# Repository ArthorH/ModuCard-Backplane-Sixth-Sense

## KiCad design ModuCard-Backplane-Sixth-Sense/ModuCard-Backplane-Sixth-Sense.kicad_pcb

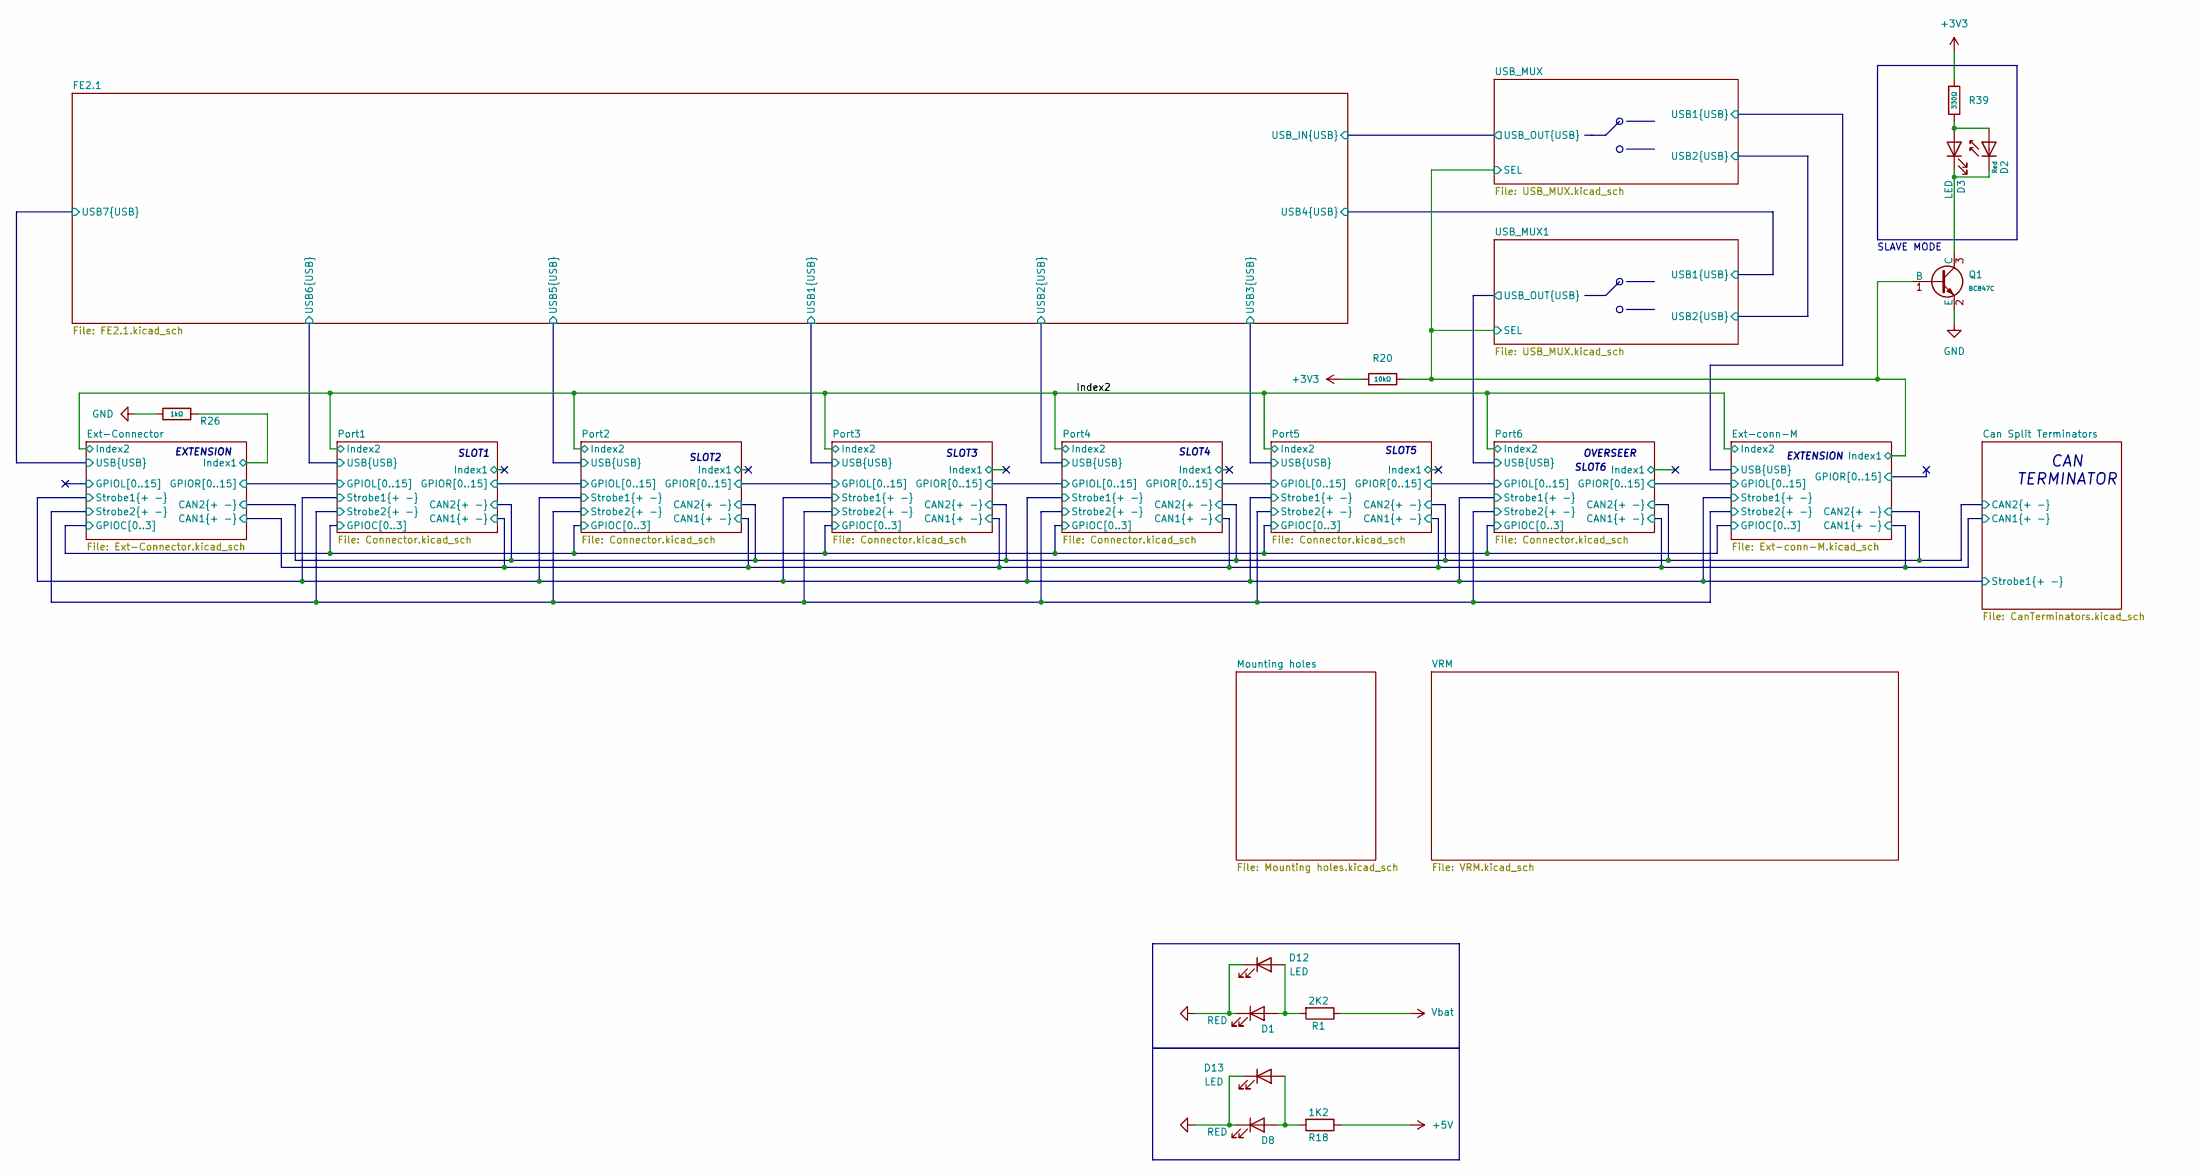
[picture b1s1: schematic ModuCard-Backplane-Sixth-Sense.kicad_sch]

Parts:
D1, D8: RED; D_0402_1005Metric
D2: Red; D_0603; Part KT-0603R; LCSC C2286
D3: LED; LED_D3.0mm_Clear
D12, D13: LED; LED_D3.0mm
Q1: BC847C; Q_SOT-23; Part BC847C; LCSC C7420337
R1: 2K2; R_0402_1005Metric
R18: 1K2; R_0402_1005Metric
R20: 10kΩ; R_0402; Overload Voltage (Max) 50V; Tolerance ±1%; Part 0402WGF1002TCE; LCSC C25744
R26: 1kΩ; R_0402; Overload Voltage (Max) 50V; Tolerance ±1%; Part 0402WGF1001TCE; LCSC C11702
R39: 330Ω; R_0402; Overload Voltage (Max) 50V; Tolerance ±1%; Part 0402WGF3300TCE; LCSC C25104

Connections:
+3V3: R20.1, R39.1; also elsewhere on the board
+5V: R18.1; also elsewhere on the board
/Ext-Connector/Index1: R26.1; also elsewhere on the board
/Ext-conn-M/Index1: Q1.1 (B), R20.2; also elsewhere on the board
GND: D1.1 (K), D8.1 (K), D12.1 (K), D13.1 (K), Q1.2 (E), R26.2; also elsewhere on the board
unnamed: D1.2 (A), D12.2 (A), R1.2
unnamed: D2.2, D3.2 (A), R39.2
unnamed: D2.1, D3.1 (K), Q1.3 (C)
unnamed: D8.2 (A), D13.2 (A), R18.2
Vbat: R1.1; also elsewhere on the board

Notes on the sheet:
CAN TERMINATOR
SLOT4
SLAVE MODE
OVERSEER
SLOT3
SLOT6
EXTENSION
SLOT2
SLOT5
SLOT1

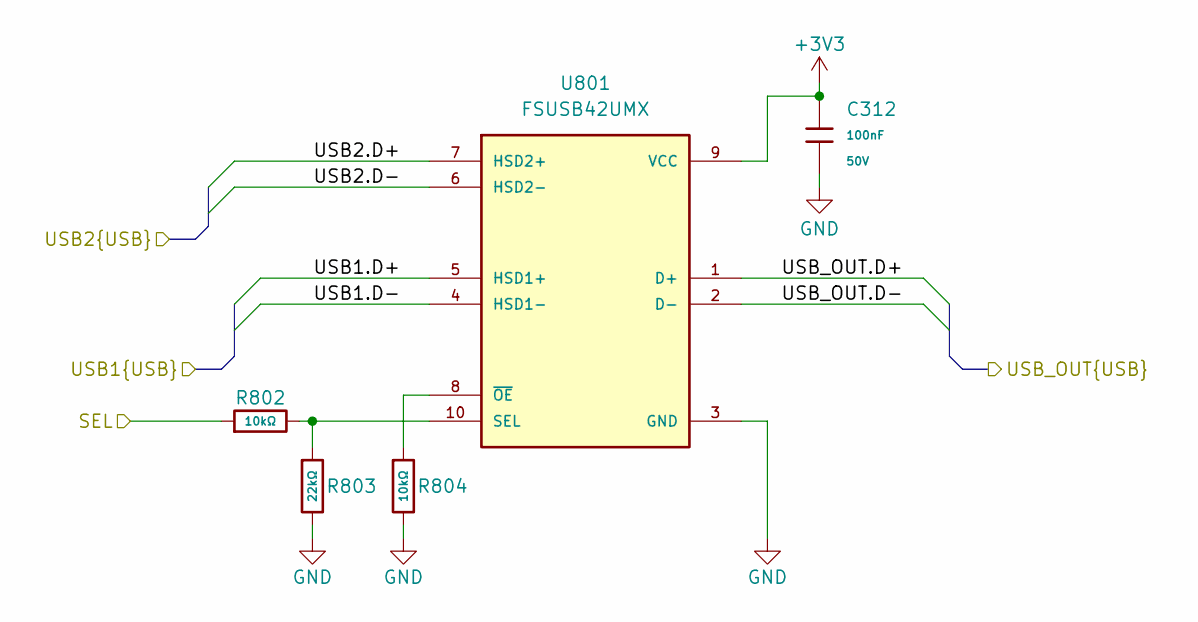
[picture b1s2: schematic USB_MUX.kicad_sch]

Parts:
C312: 100nF; C_0402; Voltage Rated 50V; Tolerance ±10%; Part CL05B104KB54PNC; LCSC C307331
R802, R804: 10kΩ; R_0402; Overload Voltage (Max) 50V; Tolerance ±1%; Part 0402WGF1002TCE; LCSC C25744
R803: 22kΩ; R_0402; Overload Voltage (Max) 50V; Tolerance ±1%; Part 0402WGF2202TCE; LCSC C25768
U801: FSUSB42UMX; UQFN-10_1.4x1.8mm_P0.4mm; PARTREV 1.25; LCSC C49186231

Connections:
+3V3: C312.1, U801.9 (VCC); also elsewhere on the board
/Ext-conn-M/Index1: R802.1; also elsewhere on the board
/Ext-conn-M/USB.D+: U801.5 (HSD1+); also elsewhere on the board
/Ext-conn-M/USB.D-: U801.4 (HSD1-); also elsewhere on the board
/FE2.1/USB_IN.D+: U801.1 (D+); also elsewhere on the board
/FE2.1/USB_IN.D-: U801.2 (D-); also elsewhere on the board
/USB_MUX/USB2.D+: U801.7 (HSD2+); also elsewhere on the board
/USB_MUX/USB2.D-: U801.6 (HSD2-); also elsewhere on the board
GND: C312.2, R803.2, R804.2, U801.3 (GND); also elsewhere on the board
unnamed: R802.2, R803.1, U801.10 (SEL)
unnamed: R804.1, U801.8 (~OE)

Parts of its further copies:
C313: 100nF; C_0402; Voltage Rated 50V; Tolerance ±10%; Part CL05B104KB54PNC; LCSC C307331
R805, R807: 10kΩ; R_0402; Overload Voltage (Max) 50V; Tolerance ±1%; Part 0402WGF1002TCE; LCSC C25744
R806: 22kΩ; R_0402; Overload Voltage (Max) 50V; Tolerance ±1%; Part 0402WGF2202TCE; LCSC C25768
U802: FSUSB42UMX; UQFN-10_1.4x1.8mm_P0.4mm; PARTREV 1.25; LCSC C49186231

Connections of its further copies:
+3V3: C313.1, U802.9 (VCC); also elsewhere on the board
/Ext-conn-M/Index1: R805.1; also elsewhere on the board
/FE2.1/USB4.D+: U802.5 (HSD1+); also elsewhere on the board
/FE2.1/USB4.D-: U802.4 (HSD1-); also elsewhere on the board
/Port6/USB.D+: U802.1 (D+); also elsewhere on the board
/Port6/USB.D-: U802.2 (D-); also elsewhere on the board
/USB_MUX/USB2.D+: U802.7 (HSD2+); also elsewhere on the board
/USB_MUX/USB2.D-: U802.6 (HSD2-); also elsewhere on the board
GND: C313.2, R806.2, R807.2, U802.3 (GND); also elsewhere on the board
unnamed: R805.2, R806.1, U802.10 (SEL)
unnamed: R807.1, U802.8 (~OE)

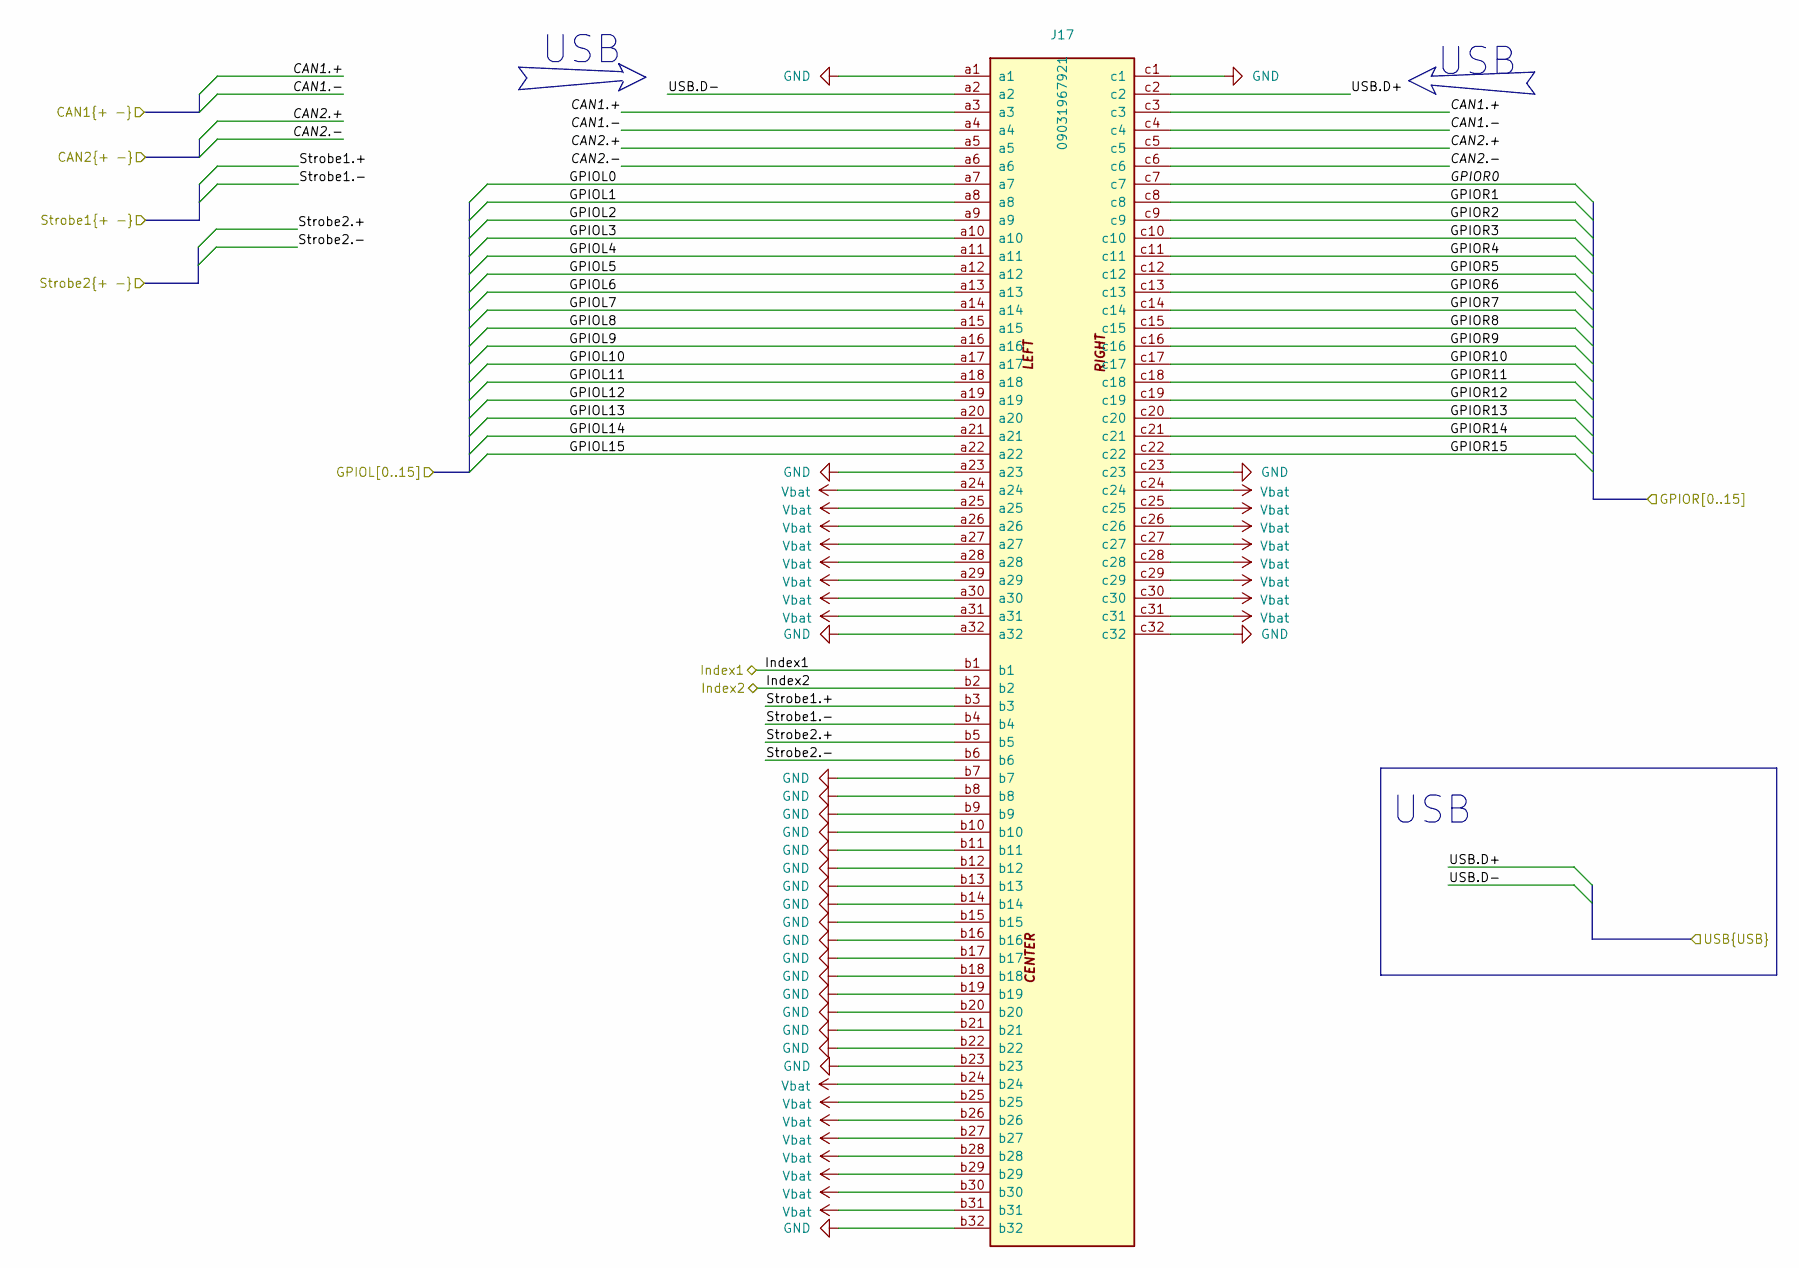
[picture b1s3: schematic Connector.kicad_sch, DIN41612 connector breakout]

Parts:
J17: 09031967921; DIN41612_R_3x32_Male_Vertical_THT; PARTREV D

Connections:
/Can Split Terminators/CAN1.+: J17.a3, J17.c3; also elsewhere on the board
/Can Split Terminators/CAN1.-: J17.a4, J17.c4; also elsewhere on the board
/Can Split Terminators/CAN2.+: J17.a5, J17.c5; also elsewhere on the board
/Can Split Terminators/CAN2.-: J17.a6, J17.c6; also elsewhere on the board
/Can Split Terminators/Strobe1.+: J17.b3; also elsewhere on the board
/Can Split Terminators/Strobe1.-: J17.b4; also elsewhere on the board
/Ext-Connector/Strobe2.+: J17.b5; also elsewhere on the board
/Ext-Connector/Strobe2.-: J17.b6; also elsewhere on the board
/FE2.1/USB5.D+: J17.c2; also elsewhere on the board
/FE2.1/USB5.D-: J17.a2; also elsewhere on the board
/Index2: J17.b2; also elsewhere on the board
/Port1/GPIOR0: J17.a7; also elsewhere on the board
/Port1/GPIOR1: J17.a8; also elsewhere on the board
/Port1/GPIOR2: J17.a9; also elsewhere on the board
/Port1/GPIOR3: J17.a10; also elsewhere on the board
/Port1/GPIOR4: J17.a11; also elsewhere on the board
/Port1/GPIOR5: J17.a12; also elsewhere on the board
/Port1/GPIOR6: J17.a13; also elsewhere on the board
/Port1/GPIOR7: J17.a14; also elsewhere on the board
/Port1/GPIOR8: J17.a15; also elsewhere on the board
/Port1/GPIOR9: J17.a16; also elsewhere on the board
/Port1/GPIOR10: J17.a17; also elsewhere on the board
/Port1/GPIOR11: J17.a18; also elsewhere on the board
/Port1/GPIOR12: J17.a19; also elsewhere on the board
/Port1/GPIOR13: J17.a20; also elsewhere on the board
/Port1/GPIOR14: J17.a21; also elsewhere on the board
/Port1/GPIOR15: J17.a22; also elsewhere on the board
/Port2/GPIOR0: J17.c7; also elsewhere on the board
/Port2/GPIOR1: J17.c8; also elsewhere on the board
/Port2/GPIOR2: J17.c9; also elsewhere on the board
/Port2/GPIOR3: J17.c10; also elsewhere on the board
/Port2/GPIOR4: J17.c11; also elsewhere on the board
/Port2/GPIOR5: J17.c12; also elsewhere on the board
/Port2/GPIOR6: J17.c13; also elsewhere on the board
/Port2/GPIOR7: J17.c14; also elsewhere on the board
/Port2/GPIOR8: J17.c15; also elsewhere on the board
/Port2/GPIOR9: J17.c16; also elsewhere on the board
/Port2/GPIOR10: J17.c17; also elsewhere on the board
/Port2/GPIOR11: J17.c18; also elsewhere on the board
/Port2/GPIOR12: J17.c19; also elsewhere on the board
/Port2/GPIOR13: J17.c20; also elsewhere on the board
/Port2/GPIOR14: J17.c21; also elsewhere on the board
/Port2/GPIOR15: J17.c22; also elsewhere on the board
/Port2/Index1: J17.b1
GND: J17.a1, J17.a23, J17.a32, J17.b7, J17.b8, J17.b9, J17.b10, J17.b11, J17.b12, J17.b13, J17.b14, J17.b15, J17.b16, J17.b17, J17.b18, J17.b19, J17.b20, J17.b21, J17.b22, J17.b23, J17.b32, J17.c1, J17.c23, J17.c32; also elsewhere on the board
Vbat: J17.a24, J17.a25, J17.a26, J17.a27, J17.a28, J17.a29, J17.a30, J17.a31, J17.b24, J17.b25, J17.b26, J17.b27, J17.b28, J17.b29, J17.b30, J17.b31, J17.c24, J17.c25, J17.c26, J17.c27, J17.c28, J17.c29, J17.c30, J17.c31; also elsewhere on the board

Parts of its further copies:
J16, J18, J19, J20, J21: 09031967921; DIN41612_R_3x32_Male_Vertical_THT; PARTREV D

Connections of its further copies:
/Can Split Terminators/CAN1.+: J16.a3, J16.c3, J18.a3, J18.c3, J19.a3, J19.c3, J20.a3, J20.c3, J21.a3, J21.c3; also elsewhere on the board
/Can Split Terminators/CAN1.-: J16.a4, J16.c4, J18.a4, J18.c4, J19.a4, J19.c4, J20.a4, J20.c4, J21.a4, J21.c4; also elsewhere on the board
/Can Split Terminators/CAN2.+: J16.a5, J16.c5, J18.a5, J18.c5, J19.a5, J19.c5, J20.a5, J20.c5, J21.a5, J21.c5; also elsewhere on the board
/Can Split Terminators/CAN2.-: J16.a6, J16.c6, J18.a6, J18.c6, J19.a6, J19.c6, J20.a6, J20.c6, J21.a6, J21.c6; also elsewhere on the board
/Can Split Terminators/Strobe1.+: J16.b3, J18.b3, J19.b3, J20.b3, J21.b3; also elsewhere on the board
/Can Split Terminators/Strobe1.-: J16.b4, J18.b4, J19.b4, J20.b4, J21.b4; also elsewhere on the board
/Ext-Connector/GPIOR0: J16.a7; also elsewhere on the board
/Ext-Connector/GPIOR1: J16.a8; also elsewhere on the board
/Ext-Connector/GPIOR2: J16.a9; also elsewhere on the board
/Ext-Connector/GPIOR3: J16.a10; also elsewhere on the board
/Ext-Connector/GPIOR4: J16.a11; also elsewhere on the board
/Ext-Connector/GPIOR5: J16.a12; also elsewhere on the board
/Ext-Connector/GPIOR6: J16.a13; also elsewhere on the board
/Ext-Connector/GPIOR7: J16.a14; also elsewhere on the board
/Ext-Connector/GPIOR8: J16.a15; also elsewhere on the board
/Ext-Connector/GPIOR9: J16.a16; also elsewhere on the board
/Ext-Connector/GPIOR10: J16.a17; also elsewhere on the board
/Ext-Connector/GPIOR11: J16.a18; also elsewhere on the board
/Ext-Connector/GPIOR12: J16.a19; also elsewhere on the board
/Ext-Connector/GPIOR13: J16.a20; also elsewhere on the board
/Ext-Connector/GPIOR14: J16.a21; also elsewhere on the board
/Ext-Connector/GPIOR15: J16.a22; also elsewhere on the board
/Ext-Connector/Strobe2.+: J16.b5, J18.b5, J19.b5, J20.b5, J21.b5; also elsewhere on the board
/Ext-Connector/Strobe2.-: J16.b6, J18.b6, J19.b6, J20.b6, J21.b6; also elsewhere on the board
/Ext-conn-M/GPIOL0: J21.c7; also elsewhere on the board
/Ext-conn-M/GPIOL1: J21.c8; also elsewhere on the board
/Ext-conn-M/GPIOL2: J21.c9; also elsewhere on the board
/Ext-conn-M/GPIOL3: J21.c10; also elsewhere on the board
/Ext-conn-M/GPIOL4: J21.c11; also elsewhere on the board
/Ext-conn-M/GPIOL5: J21.c12; also elsewhere on the board
/Ext-conn-M/GPIOL6: J21.c13; also elsewhere on the board
/Ext-conn-M/GPIOL7: J21.c14; also elsewhere on the board
/Ext-conn-M/GPIOL8: J21.c15; also elsewhere on the board
/Ext-conn-M/GPIOL9: J21.c16; also elsewhere on the board
/Ext-conn-M/GPIOL10: J21.c17; also elsewhere on the board
/Ext-conn-M/GPIOL11: J21.c18; also elsewhere on the board
/Ext-conn-M/GPIOL12: J21.c19; also elsewhere on the board
/Ext-conn-M/GPIOL13: J21.c20; also elsewhere on the board
/Ext-conn-M/GPIOL14: J21.c21; also elsewhere on the board
/Ext-conn-M/GPIOL15: J21.c22; also elsewhere on the board
/FE2.1/USB1.D+: J18.c2; also elsewhere on the board
/FE2.1/USB1.D-: J18.a2; also elsewhere on the board
/FE2.1/USB2.D+: J19.c2; also elsewhere on the board
/FE2.1/USB2.D-: J19.a2; also elsewhere on the board
/FE2.1/USB3.D+: J20.c2; also elsewhere on the board
/FE2.1/USB3.D-: J20.a2; also elsewhere on the board
/FE2.1/USB6.D+: J16.c2; also elsewhere on the board
/FE2.1/USB6.D-: J16.a2; also elsewhere on the board
/Index2: J16.b2, J18.b2, J19.b2, J20.b2, J21.b2; also elsewhere on the board
/Port1/GPIOR0: J16.c7; also elsewhere on the board
/Port1/GPIOR1: J16.c8; also elsewhere on the board
/Port1/GPIOR2: J16.c9; also elsewhere on the board
/Port1/GPIOR3: J16.c10; also elsewhere on the board
/Port1/GPIOR4: J16.c11; also elsewhere on the board
/Port1/GPIOR5: J16.c12; also elsewhere on the board
/Port1/GPIOR6: J16.c13; also elsewhere on the board
/Port1/GPIOR7: J16.c14; also elsewhere on the board
/Port1/GPIOR8: J16.c15; also elsewhere on the board
/Port1/GPIOR9: J16.c16; also elsewhere on the board
/Port1/GPIOR10: J16.c17; also elsewhere on the board
/Port1/GPIOR11: J16.c18; also elsewhere on the board
/Port1/GPIOR12: J16.c19; also elsewhere on the board
/Port1/GPIOR13: J16.c20; also elsewhere on the board
/Port1/GPIOR14: J16.c21; also elsewhere on the board
/Port1/GPIOR15: J16.c22; also elsewhere on the board
/Port1/Index1: J16.b1
/Port2/GPIOR0: J18.a7; also elsewhere on the board
/Port2/GPIOR1: J18.a8; also elsewhere on the board
/Port2/GPIOR2: J18.a9; also elsewhere on the board
/Port2/GPIOR3: J18.a10; also elsewhere on the board
/Port2/GPIOR4: J18.a11; also elsewhere on the board
/Port2/GPIOR5: J18.a12; also elsewhere on the board
/Port2/GPIOR6: J18.a13; also elsewhere on the board
/Port2/GPIOR7: J18.a14; also elsewhere on the board
/Port2/GPIOR8: J18.a15; also elsewhere on the board
/Port2/GPIOR9: J18.a16; also elsewhere on the board
/Port2/GPIOR10: J18.a17; also elsewhere on the board
/Port2/GPIOR11: J18.a18; also elsewhere on the board
/Port2/GPIOR12: J18.a19; also elsewhere on the board
/Port2/GPIOR13: J18.a20; also elsewhere on the board
/Port2/GPIOR14: J18.a21; also elsewhere on the board
/Port2/GPIOR15: J18.a22; also elsewhere on the board
/Port3/GPIOR0: J18.c7, J19.a7
/Port3/GPIOR1: J18.c8, J19.a8
/Port3/GPIOR2: J18.c9, J19.a9
/Port3/GPIOR3: J18.c10, J19.a10
/Port3/GPIOR4: J18.c11, J19.a11
/Port3/GPIOR5: J18.c12, J19.a12
/Port3/GPIOR6: J18.c13, J19.a13
/Port3/GPIOR7: J18.c14, J19.a14
/Port3/GPIOR8: J18.c15, J19.a15
/Port3/GPIOR9: J18.c16, J19.a16
/Port3/GPIOR10: J18.c17, J19.a17
/Port3/GPIOR11: J18.c18, J19.a18
/Port3/GPIOR12: J18.c19, J19.a19
/Port3/GPIOR13: J18.c20, J19.a20
/Port3/GPIOR14: J18.c21, J19.a21
/Port3/GPIOR15: J18.c22, J19.a22
/Port3/Index1: J18.b1
/Port4/GPIOR0: J19.c7, J20.a7
/Port4/GPIOR1: J19.c8, J20.a8
/Port4/GPIOR2: J19.c9, J20.a9
/Port4/GPIOR3: J19.c10, J20.a10
/Port4/GPIOR4: J19.c11, J20.a11
/Port4/GPIOR5: J19.c12, J20.a12
/Port4/GPIOR6: J19.c13, J20.a13
/Port4/GPIOR7: J19.c14, J20.a14
/Port4/GPIOR8: J19.c15, J20.a15
/Port4/GPIOR9: J19.c16, J20.a16
/Port4/GPIOR10: J19.c17, J20.a17
/Port4/GPIOR11: J19.c18, J20.a18
/Port4/GPIOR12: J19.c19, J20.a19
/Port4/GPIOR13: J19.c20, J20.a20
/Port4/GPIOR14: J19.c21, J20.a21
/Port4/GPIOR15: J19.c22, J20.a22
/Port4/Index1: J19.b1
/Port5/GPIOR0: J20.c7, J21.a7
/Port5/GPIOR1: J20.c8, J21.a8
/Port5/GPIOR2: J20.c9, J21.a9
/Port5/GPIOR3: J20.c10, J21.a10
/Port5/GPIOR4: J20.c11, J21.a11
/Port5/GPIOR5: J20.c12, J21.a12
/Port5/GPIOR6: J20.c13, J21.a13
/Port5/GPIOR7: J20.c14, J21.a14
/Port5/GPIOR8: J20.c15, J21.a15
/Port5/GPIOR9: J20.c16, J21.a16
/Port5/GPIOR10: J20.c17, J21.a17
/Port5/GPIOR11: J20.c18, J21.a18
/Port5/GPIOR12: J20.c19, J21.a19
/Port5/GPIOR13: J20.c20, J21.a20
/Port5/GPIOR14: J20.c21, J21.a21
/Port5/GPIOR15: J20.c22, J21.a22
/Port5/Index1: J20.b1
/Port6/Index1: J21.b1
/Port6/USB.D+: J21.c2; also elsewhere on the board
/Port6/USB.D-: J21.a2; also elsewhere on the board
GND: J16.a1, J16.a23, J16.a32, J16.b7, J16.b8, J16.b9, J16.b10, J16.b11, J16.b12, J16.b13, J16.b14, J16.b15, J16.b16, J16.b17, J16.b18, J16.b19, J16.b20, J16.b21, J16.b22, J16.b23, J16.b32, J16.c1, J16.c23, J16.c32, J18.a1, J18.a23, J18.a32, J18.b7, J18.b8, J18.b9, J18.b10, J18.b11, J18.b12, J18.b13, J18.b14, J18.b15, J18.b16, J18.b17, J18.b18, J18.b19, J18.b20, J18.b21, J18.b22, J18.b23, J18.b32, J18.c1, J18.c23, J18.c32, J19.a1, J19.a23, J19.a32, J19.b7, J19.b8, J19.b9, J19.b10, J19.b11, J19.b12, J19.b13, J19.b14, J19.b15, J19.b16, J19.b17, J19.b18, J19.b19, J19.b20, J19.b21, J19.b22, J19.b23, J19.b32, J19.c1, J19.c23, J19.c32, J20.a1, J20.a23, J20.a32, J20.b7, J20.b8, J20.b9, J20.b10, J20.b11, J20.b12, J20.b13, J20.b14, J20.b15, J20.b16, J20.b17, J20.b18, J20.b19, J20.b20, J20.b21, J20.b22, J20.b23, J20.b32, J20.c1, J20.c23, J20.c32, J21.a1, J21.a23, J21.a32, J21.b7, J21.b8, J21.b9, J21.b10, J21.b11, J21.b12, J21.b13, J21.b14, J21.b15, J21.b16, J21.b17, J21.b18, J21.b19, J21.b20, J21.b21, J21.b22, J21.b23, J21.b32, J21.c1, J21.c23, J21.c32; also elsewhere on the board
Vbat: J16.a24, J16.a25, J16.a26, J16.a27, J16.a28, J16.a29, J16.a30, J16.a31, J16.b24, J16.b25, J16.b26, J16.b27, J16.b28, J16.b29, J16.b30, J16.b31, J16.c24, J16.c25, J16.c26, J16.c27, J16.c28, J16.c29, J16.c30, J16.c31, J18.a24, J18.a25, J18.a26, J18.a27, J18.a28, J18.a29, J18.a30, J18.a31, J18.b24, J18.b25, J18.b26, J18.b27, J18.b28, J18.b29, J18.b30, J18.b31, J18.c24, J18.c25, J18.c26, J18.c27, J18.c28, J18.c29, J18.c30, J18.c31, J19.a24, J19.a25, J19.a26, J19.a27, J19.a28, J19.a29, J19.a30, J19.a31, J19.b24, J19.b25, J19.b26, J19.b27, J19.b28, J19.b29, J19.b30, J19.b31, J19.c24, J19.c25, J19.c26, J19.c27, J19.c28, J19.c29, J19.c30, J19.c31, J20.a24, J20.a25, J20.a26, J20.a27, J20.a28, J20.a29, J20.a30, J20.a31, J20.b24, J20.b25, J20.b26, J20.b27, J20.b28, J20.b29, J20.b30, J20.b31, J20.c24, J20.c25, J20.c26, J20.c27, J20.c28, J20.c29, J20.c30, J20.c31, J21.a24, J21.a25, J21.a26, J21.a27, J21.a28, J21.a29, J21.a30, J21.a31, J21.b24, J21.b25, J21.b26, J21.b27, J21.b28, J21.b29, J21.b30, J21.b31, J21.c24, J21.c25, J21.c26, J21.c27, J21.c28, J21.c29, J21.c30, J21.c31; also elsewhere on the board

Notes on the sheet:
USB

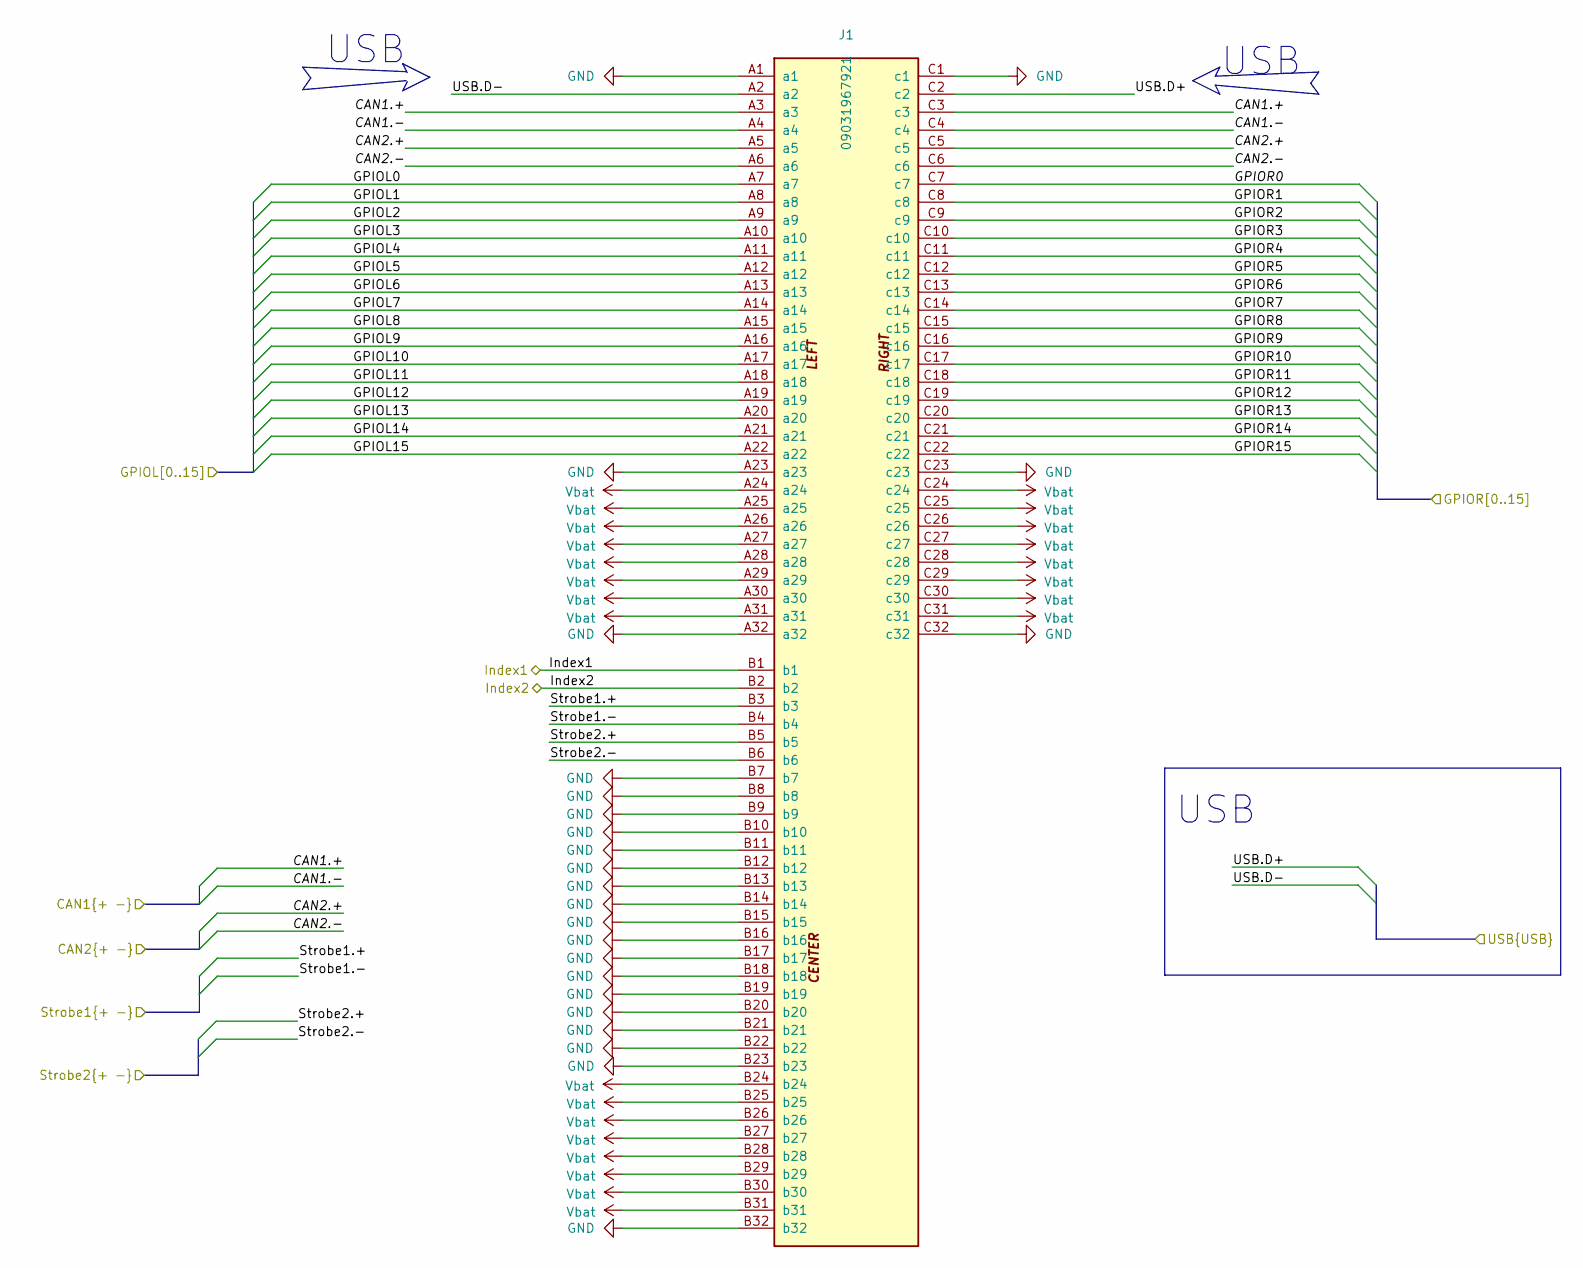
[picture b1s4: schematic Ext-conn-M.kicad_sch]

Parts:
J1: 09031967921; PARTREV D

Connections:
/Can Split Terminators/CAN1.+: J1.A3 (a3), J1.C3 (c3); also elsewhere on the board
/Can Split Terminators/CAN1.-: J1.A4 (a4), J1.C4 (c4); also elsewhere on the board
/Can Split Terminators/CAN2.+: J1.A5 (a5), J1.C5 (c5); also elsewhere on the board
/Can Split Terminators/CAN2.-: J1.A6 (a6), J1.C6 (c6); also elsewhere on the board
/Can Split Terminators/Strobe1.+: J1.B3 (b3); also elsewhere on the board
/Can Split Terminators/Strobe1.-: J1.B4 (b4); also elsewhere on the board
/Ext-Connector/Strobe2.+: J1.B5 (b5); also elsewhere on the board
/Ext-Connector/Strobe2.-: J1.B6 (b6); also elsewhere on the board
/Ext-conn-M/GPIOL0: J1.A7 (a7); also elsewhere on the board
/Ext-conn-M/GPIOL1: J1.A8 (a8); also elsewhere on the board
/Ext-conn-M/GPIOL2: J1.A9 (a9); also elsewhere on the board
/Ext-conn-M/GPIOL3: J1.A10 (a10); also elsewhere on the board
/Ext-conn-M/GPIOL4: J1.A11 (a11); also elsewhere on the board
/Ext-conn-M/GPIOL5: J1.A12 (a12); also elsewhere on the board
/Ext-conn-M/GPIOL6: J1.A13 (a13); also elsewhere on the board
/Ext-conn-M/GPIOL7: J1.A14 (a14); also elsewhere on the board
/Ext-conn-M/GPIOL8: J1.A15 (a15); also elsewhere on the board
/Ext-conn-M/GPIOL9: J1.A16 (a16); also elsewhere on the board
/Ext-conn-M/GPIOL10: J1.A17 (a17); also elsewhere on the board
/Ext-conn-M/GPIOL11: J1.A18 (a18); also elsewhere on the board
/Ext-conn-M/GPIOL12: J1.A19 (a19); also elsewhere on the board
/Ext-conn-M/GPIOL13: J1.A20 (a20); also elsewhere on the board
/Ext-conn-M/GPIOL14: J1.A21 (a21); also elsewhere on the board
/Ext-conn-M/GPIOL15: J1.A22 (a22); also elsewhere on the board
/Ext-conn-M/GPIOR0: J1.C7 (c7)
/Ext-conn-M/GPIOR1: J1.C8 (c8)
/Ext-conn-M/GPIOR2: J1.C9 (c9)
/Ext-conn-M/GPIOR3: J1.C10 (c10)
/Ext-conn-M/GPIOR4: J1.C11 (c11)
/Ext-conn-M/GPIOR5: J1.C12 (c12)
/Ext-conn-M/GPIOR6: J1.C13 (c13)
/Ext-conn-M/GPIOR7: J1.C14 (c14)
/Ext-conn-M/GPIOR8: J1.C15 (c15)
/Ext-conn-M/GPIOR9: J1.C16 (c16)
/Ext-conn-M/GPIOR10: J1.C17 (c17)
/Ext-conn-M/GPIOR11: J1.C18 (c18)
/Ext-conn-M/GPIOR12: J1.C19 (c19)
/Ext-conn-M/GPIOR13: J1.C20 (c20)
/Ext-conn-M/GPIOR14: J1.C21 (c21)
/Ext-conn-M/GPIOR15: J1.C22 (c22)
/Ext-conn-M/Index1: J1.B1 (b1); also elsewhere on the board
/Ext-conn-M/USB.D+: J1.C2 (c2); also elsewhere on the board
/Ext-conn-M/USB.D-: J1.A2 (a2); also elsewhere on the board
/Index2: J1.B2 (b2); also elsewhere on the board
GND: J1.A1 (a1), J1.A23 (a23), J1.A32 (a32), J1.B7 (b7), J1.B8 (b8), J1.B9 (b9), J1.B10 (b10), J1.B11 (b11), J1.B12 (b12), J1.B13 (b13), J1.B14 (b14), J1.B15 (b15), J1.B16 (b16), J1.B17 (b17), J1.B18 (b18), J1.B19 (b19), J1.B20 (b20), J1.B21 (b21), J1.B22 (b22), J1.B23 (b23), J1.B32 (b32), J1.C1 (c1), J1.C23 (c23), J1.C32 (c32); also elsewhere on the board
Vbat: J1.A24 (a24), J1.A25 (a25), J1.A26 (a26), J1.A27 (a27), J1.A28 (a28), J1.A29 (a29), J1.A30 (a30), J1.A31 (a31), J1.B24 (b24), J1.B25 (b25), J1.B26 (b26), J1.B27 (b27), J1.B28 (b28), J1.B29 (b29), J1.B30 (b30), J1.B31 (b31), J1.C24 (c24), J1.C25 (c25), J1.C26 (c26), J1.C27 (c27), J1.C28 (c28), J1.C29 (c29), J1.C30 (c30), J1.C31 (c31); also elsewhere on the board

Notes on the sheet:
USB

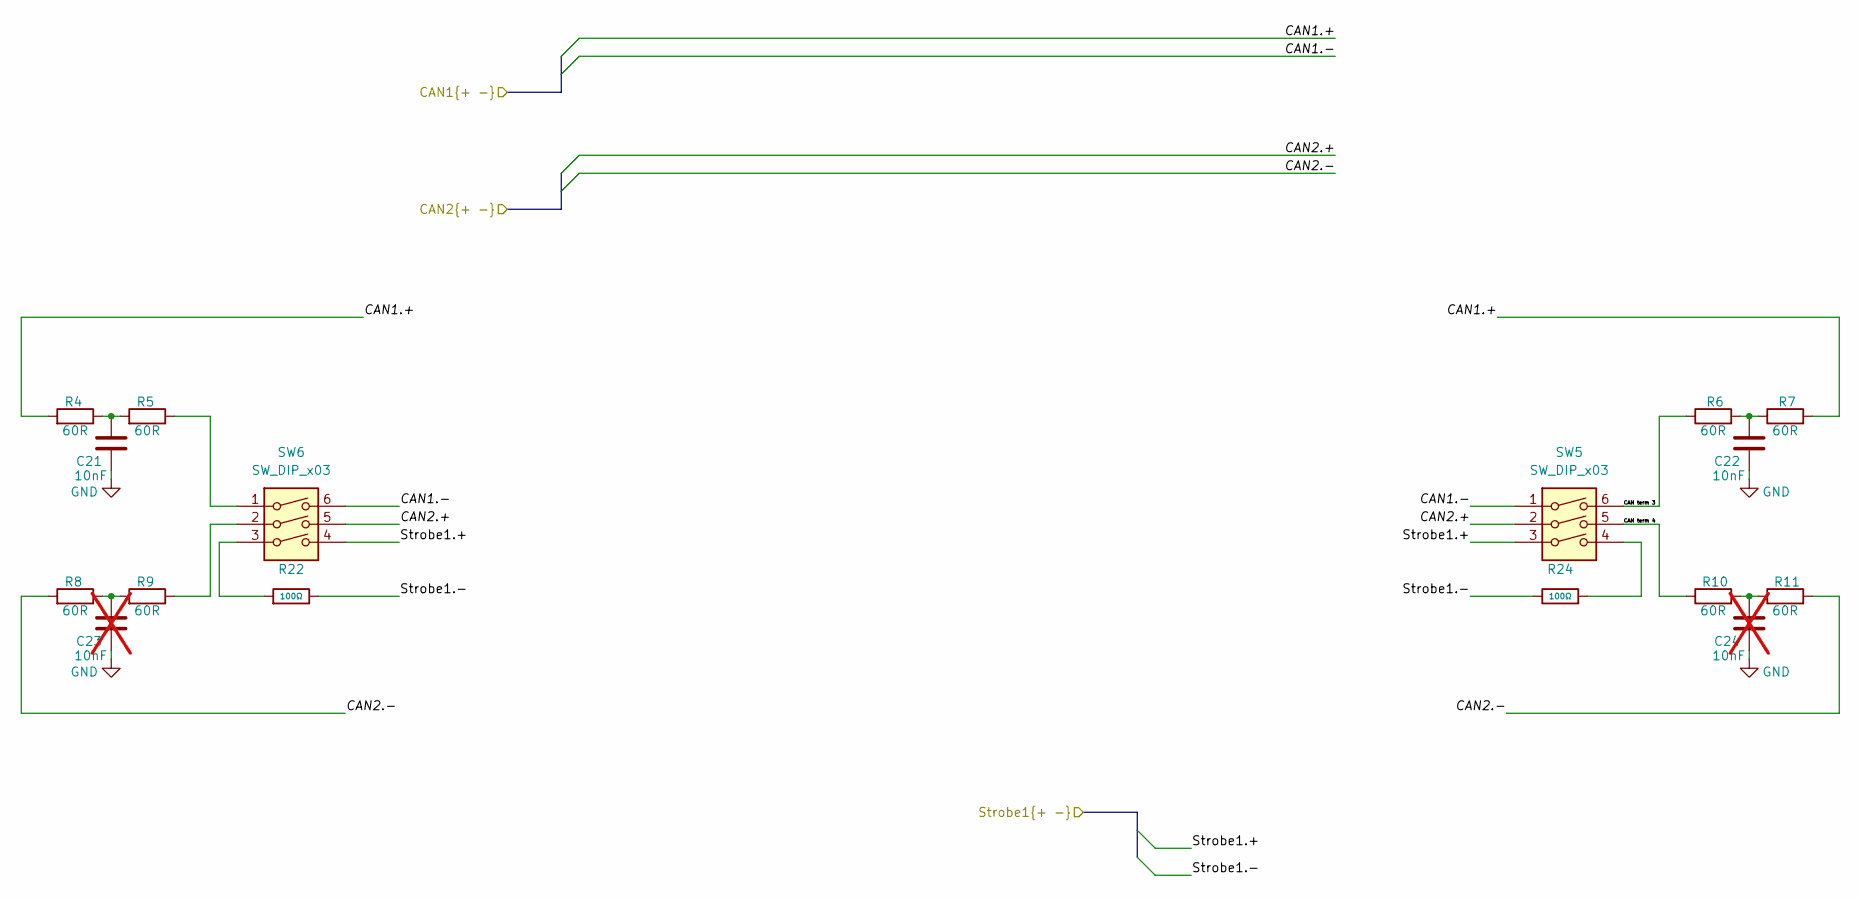
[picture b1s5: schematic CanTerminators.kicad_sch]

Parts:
C21, C22: 10nF; C_0402_1005Metric
C23, C24: 10nF; C_0402_1005Metric; not fitted
R4, R5, R6, R7, R8, R9, R10, R11: 60R; R_0402_1005Metric
R22, R24: 100Ω; R_0603; Overload Voltage (Max) 75V; Tolerance ±1%; Part 0603WAF1000T5E; LCSC C22775
SW5, SW6: SW_DIP_x03; SW_DIP_SPSTx03_Slide_6.7x9.18mm_W7.62mm_P2.54mm_LowProfile

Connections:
/Can Split Terminators/CAN1.+: R4.2, R7.2; also elsewhere on the board
/Can Split Terminators/CAN1.-: SW5.1, SW6.6; also elsewhere on the board
/Can Split Terminators/CAN2.+: SW5.2, SW6.5; also elsewhere on the board
/Can Split Terminators/CAN2.-: R8.2, R11.2; also elsewhere on the board
/Can Split Terminators/CAN term 3: R6.1, SW5.6
/Can Split Terminators/CAN term 4: R10.1, SW5.5
/Can Split Terminators/Strobe1.+: SW5.3, SW6.4; also elsewhere on the board
/Can Split Terminators/Strobe1.-: R22.2, R24.2; also elsewhere on the board
GND: C21.2, C22.2, C23.2, C24.2; also elsewhere on the board
unnamed: C21.1, R4.1, R5.2
unnamed: C22.1, R6.2, R7.1
unnamed: C23.1, R8.1, R9.2
unnamed: C24.1, R10.2, R11.1
unnamed: R5.1, SW6.1
unnamed: R9.1, SW6.2
unnamed: R22.1, SW6.3
unnamed: R24.1, SW5.4

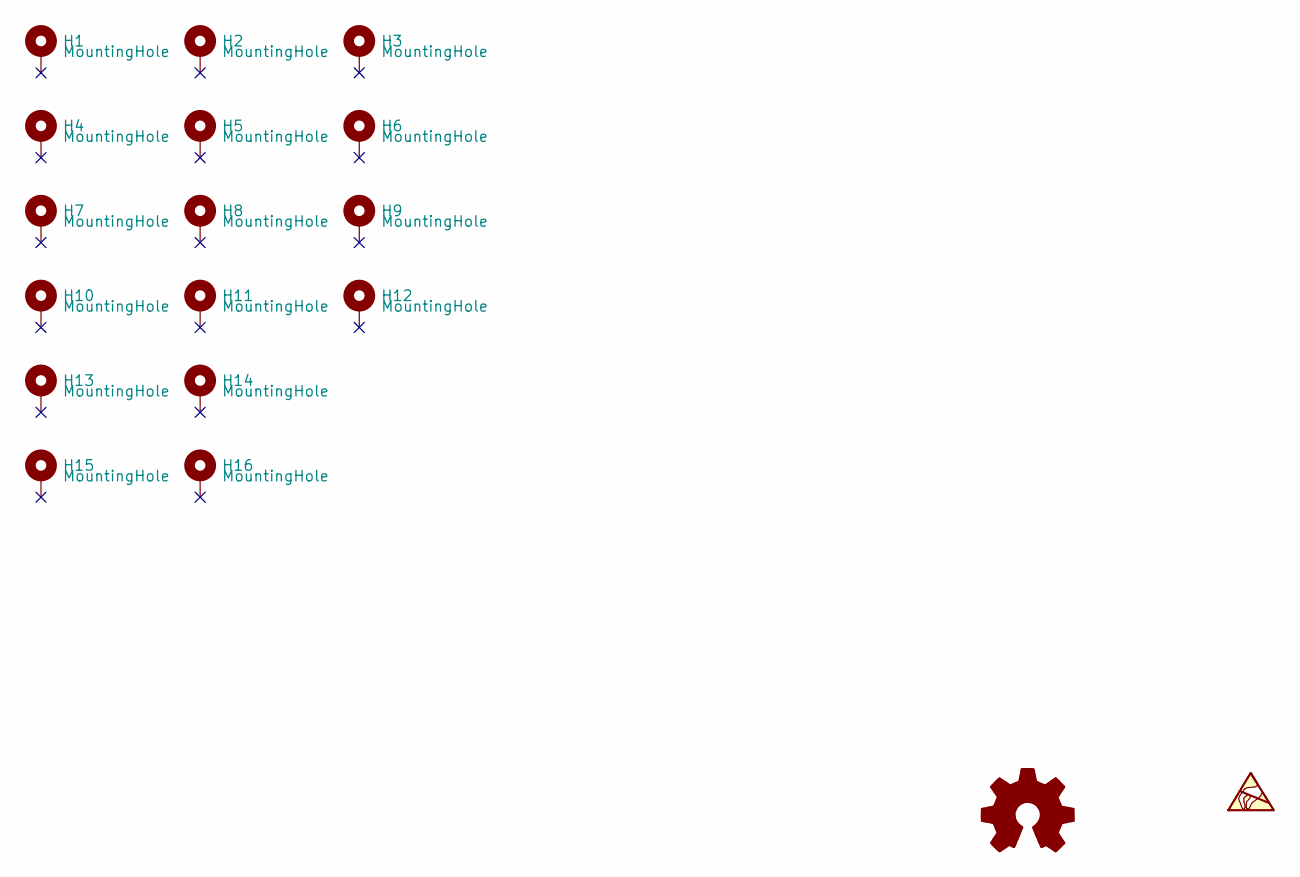
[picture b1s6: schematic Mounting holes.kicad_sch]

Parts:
H1, H2, H3, H4, H5, H6, H7, H8, H9, H10, H11, H12, H13, H14, H15, H16: MountingHole; MountingHole_2.7mm_M2.5_DIN965_Pad
